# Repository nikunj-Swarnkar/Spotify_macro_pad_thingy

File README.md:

# Spotify Macro-pad Thingy

A custom key macropad with two rotating dials, 6 customisable keys, and an OLED screen. Basically my iteration of the Spotify car thing — but for your desk.

**Project by [nikunj-Swarnkar](https://github.com/nikunj-Swarnkar)** — Firmware by [Nitin-2468-dev](https://github.com/Nitin-2468-dev)

---

## Features

- Two-part case, easy to assemble
- 128×32 OLED display
- 2 × EC11 rotary encoders
- 4 heat-set inserts and bolted case
- 6 mechanical keys

---

## CAD Model

Made in Fusion360. Everything fits together using 4 × M3 bolts and heat-set inserts. The case has two parts: a main body and a front lid.

---

## PCB

Made in KiCad.

**Schematic**

**PCB**

Uses MX-style key switches.

---

## Firmware Overview

The Spotify Marcro-pad Thingy runs **[KMK firmware](https://github.com/KMKfw/kmk_firmware)** on a **[Seeed XIAO RP2040](https://wiki.seeedstudio.com/XIAO-RP2040/)**, paired with a **Python bridge application** that connects Spotify playback data to the keyboard over USB. The device behaves like a mini StreamDeck dedicated to music control.

### Playback Controls

| Key        | Action          |
| ---------- | --------------- |
| Play/Pause | Toggle playback |
| Next       | Next track      |
| Previous   | Previous track  |
| Shuffle    | Toggle shuffle  |
| Repeat     | Toggle repeat   |
| Mute       | Set volume to 0 |

### Encoder Controls

| Encoder   | Function       |
| --------- | -------------- |
| Encoder 1 | Track timeline |
| Encoder 2 | Volume         |

### Key Layout

```
[ Like ]     [ Shuffle ]    [ Minimize ]
[ Rewind ]   [ Play/Pause ] [ Skip ]
```

---

## OLED Display

### Spotify Screen

```
Spotify
Blinding Lights
████░░░░░░ 1:42
```

Displays song title, playback progress bar, and current playback time.

### Volume Screen

```
Volume
██████░░░░ 60%
```

Displayed when adjusting volume.

### Idle Screen

An animated BongoCat appears when nothing is playing.

---

## Album Art Rendering

Album art is fetched from Spotify and processed by the bridge:

1. Download image
2. Resize to 32×32
3. Convert to monochrome
4. Send bitmap to keyboard

The OLED displays the artwork beside the track information.

---

## System Architecture

```
Spotify App
      ↓
Spotify Web API
      ↓
spotify_bridge.exe (Python)
      ↓
USB Serial
      ↓
KMK Firmware
      ↓
Macropad Hardware
      ↓
OLED Display + Controls
```

The bridge application handles Spotify API communication; the firmware handles hardware interaction.

---

## Serial Protocol

Communication between the firmware and bridge uses a lightweight text protocol:

```
SONG|title|artist|position|duration|tempo
VOL|70
IDLE
COVER|bitmap_data
CMD|NEXT
CMD|PLAY
CMD|SEEK|120
```

---

## Firmware

Written using **KMK (Keyboard Module Kit)** on CircuitPython. Main file: `CIRCUITPY/code.py`

**Responsibilities:**

- Scan key matrix
- Handle rotary encoders
- Communicate with bridge over USB
- Render OLED interface
- Control RGB lighting

### Pin Mapping

**Matrix**

| Function | Pin       |
| -------- | --------- |
| COL 0    | D2 / GP28 |
| COL 1    | D3 / GP29 |
| COL 2    | D10 / GP3 |
| ROW 0    | D7 / GP1  |
| ROW 1    | D8 / GP2  |

**Encoder 1 — Volume**

| Signal | Pin       |
| ------ | --------- |
| A      | D0 / GP26 |
| B      | D1 / GP27 |

**Encoder 2 — Track Scrub**

| Signal | Pin      |
| ------ | -------- |
| A      | D6 / GP0 |
| B      | D9 / GP4 |

**OLED**

| Signal | Pin      |
| ------ | -------- |
| SDA    | D4 / GP6 |
| SCL    | D5 / GP7 |

**RGB LEDs:** DATA → D0 / GP26

---

## Folder Structure

| Path | Description |
| ---- | ----------- |
| [`LICENSE`](https://github.com/nikunj-Swarnkar/Spotify_marcro_pad_thingy/blob/main/LICENSE) | MIT License |
| [`README.md`](https://github.com/nikunj-Swarnkar/Spotify_marcro_pad_thingy/blob/main/README.md) | This file |
| [`CIRCUITPY/`](https://github.com/nikunj-Swarnkar/Spotify_marcro_pad_thingy/tree/main/CIRCUITPY) | Firmware files copied to the board |
| [`CIRCUITPY/code.py`](https://github.com/nikunj-Swarnkar/Spotify_marcro_pad_thingy/blob/main/CIRCUITPY/code.py) | Main firmware entry point |
| [`CIRCUITPY/display_manager.py`](https://github.com/nikunj-Swarnkar/Spotify_marcro_pad_thingy/blob/main/CIRCUITPY/display_manager.py) | OLED display logic |
| [`CIRCUITPY/duck_animation.py`](https://github.com/nikunj-Swarnkar/Spotify_marcro_pad_thingy/blob/main/CIRCUITPY/duck_animation.py) | Idle duck animation |
| [`CIRCUITPY/rgb_manager.py`](https://github.com/nikunj-Swarnkar/Spotify_marcro_pad_thingy/blob/main/CIRCUITPY/rgb_manager.py) | RGB LED control |
| [`CIRCUITPY/lib/`](https://github.com/nikunj-Swarnkar/Spotify_marcro_pad_thingy/tree/main/CIRCUITPY/lib) | CircuitPython libraries |
| [`spotify_bridge/`](https://github.com/nikunj-Swarnkar/Spotify_marcro_pad_thingy/tree/main/spotify_bridge) | PC bridge application |
| [`spotify_bridge/spotify_bridge.exe`](https://github.com/nikunj-Swarnkar/Spotify_marcro_pad_thingy/blob/main/spotify_bridge/spotify_bridge.exe) | Compiled bridge (no Python required) |
| [`spotify_bridge/code/spotify_bridge.py`](https://github.com/nikunj-Swarnkar/Spotify_marcro_pad_thingy/blob/main/spotify_bridge/code/spotify_bridge.py) | Bridge source code |
| [`spotify_bridge/code/oled_test_app.py`](https://github.com/nikunj-Swarnkar/Spotify_marcro_pad_thingy/blob/main/spotify_bridge/code/oled_test_app.py) | OLED test utility |
| [`spotify_bridge/code/build_exe.py`](https://github.com/nikunj-Swarnkar/Spotify_marcro_pad_thingy/blob/main/spotify_bridge/code/build_exe.py) | Script to compile the bridge |
| [`spotify_bridge/res/config.json.eg`](https://github.com/nikunj-Swarnkar/Spotify_marcro_pad_thingy/blob/main/spotify_bridge/res/config.json.eg) | Example Spotify API config |
| [`spotify_bridge/res/oled_test_app.exe`](https://github.com/nikunj-Swarnkar/Spotify_marcro_pad_thingy/blob/main/spotify_bridge/res/oled_test_app.exe) | Compiled OLED test utility |
| [`spotify_bridge/res/Duck.gif`](https://github.com/nikunj-Swarnkar/Spotify_marcro_pad_thingy/blob/main/spotify_bridge/res/Duck.gif) | Duck idle animation asset |

---

## Installing Firmware

1. Install CircuitPython for the XIAO RP2040:
   [XIAO RP2040 CircuitPython Guide](https://wiki.seeedstudio.com/XIAO-RP2040-with-CircuitPython/)

2. Copy firmware files to the board at `CIRCUITPY/`.

---

## Spotify Bridge

The bridge software connects the keyboard to Spotify.

**Location:** `spotify_bridge/`

**Run:**

```
spotify_bridge.exe
```

Or:

```
python spotify_bridge.py
```

### Spotify API Setup

1. Create an application at the [Spotify Developer Dashboard](https://developer.spotify.com/dashboard)
2. Add the redirect URI: `http://localhost:8888/callback`
3. Copy your credentials into `spotify_bridge/res/config.json`

---

## Running the System

1. Plug the macropad into USB
2. Launch `spotify_bridge.exe`
3. Start Spotify
4. Use the macropad to control playback

---

## Future Improvements

- Audio visualizer on OLED
- RGB BPM lighting improvements
- System tray bridge application
- Multi-service support (YouTube Music, Apple Music)
- Enhanced OLED UI

---

## Bill of Materials

| Qty | Item                      |
| --- | ------------------------- |
| 6×  | Cherry MX switches        |
| 6×  | DSA keycaps               |
| 4×  | M3×5×4 heat-set inserts   |
| 4×  | M3×16mm SHCS bolts        |
| 6×  | 1N4148 DO-35 diodes       |
| 1×  | 0.91" 128×32 OLED display |
| 2×  | EC11 rotary encoders      |
| 1×  | Seeed XIAO RP2040         |
| 1×  | Case (2 printed parts)    |

---

## License

[MIT License](https://github.com/nikunj-Swarnkar/Spotify_marcro_pad_thingy/blob/main/LICENSE)

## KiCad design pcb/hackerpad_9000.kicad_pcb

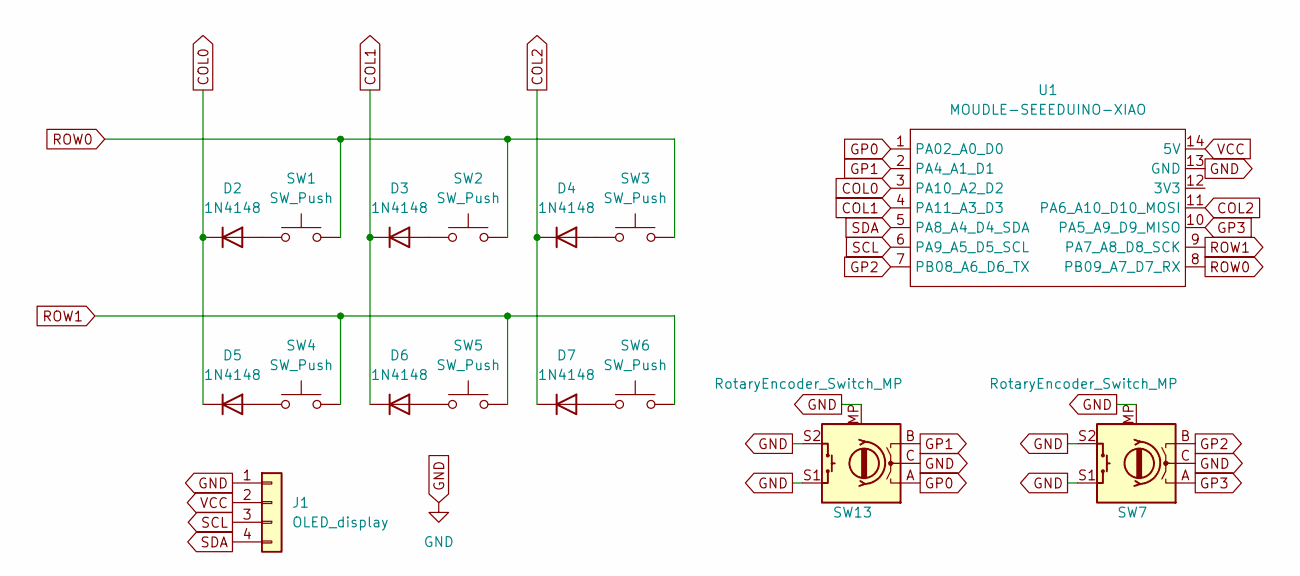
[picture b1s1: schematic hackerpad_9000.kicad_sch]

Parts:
D2, D3, D4, D5, D6, D7: 1N4148; D_DO-35_SOD27_P7.62mm_Horizontal
J1: OLED_display; SSD1306-0.91-OLED-4pin-128x32
SW1, SW2, SW3, SW4, SW5, SW6: SW_Push; SW_Cherry_MX_1.00u_PCB
SW7, SW13: RotaryEncoder_Switch_MP; RotaryEncoder_Alps_EC11E-Switch_Vertical_H20mm
U1: MOUDLE-SEEEDUINO-XIAO; XIAO-Generic-Hybrid-14P-2.54-21X17.8MM

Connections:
COL0: D2.1 (K), D5.1 (K), U1.3 (PA10_A2_D2)
COL1: D3.1 (K), D6.1 (K), U1.4 (PA11_A3_D3)
COL2: D4.1 (K), D7.1 (K), U1.11 (PA6_A10_D10_MOSI)
GND: J1.1 (GND), SW7.C, SW7.MP, SW7.S1, SW7.S2, SW13.C, SW13.MP, SW13.S1, SW13.S2, U1.13 (GND)
GP0: SW13.A, U1.1 (PA02_A0_D0)
GP1: SW13.B, U1.2 (PA4_A1_D1)
GP2: SW7.B, U1.7 (PB08_A6_D6_TX)
GP3: SW7.A, U1.10 (PA5_A9_D9_MISO)
unnamed: D2.2 (A), SW1.1
unnamed: D3.2 (A), SW2.1
unnamed: D4.2 (A), SW3.1
unnamed: D5.2 (A), SW4.1
unnamed: D6.2 (A), SW5.1
unnamed: D7.2 (A), SW6.1
ROW0: SW1.2, SW2.2, SW3.2, U1.8 (PB09_A7_D7_RX)
ROW1: SW4.2, SW5.2, SW6.2, U1.9 (PA7_A8_D8_SCK)
SCL: J1.3 (SCL), U1.6 (PA9_A5_D5_SCL)
SDA: J1.4 (SDA), U1.5 (PA8_A4_D4_SDA)
VCC: J1.2 (VCC), U1.14 (5V)

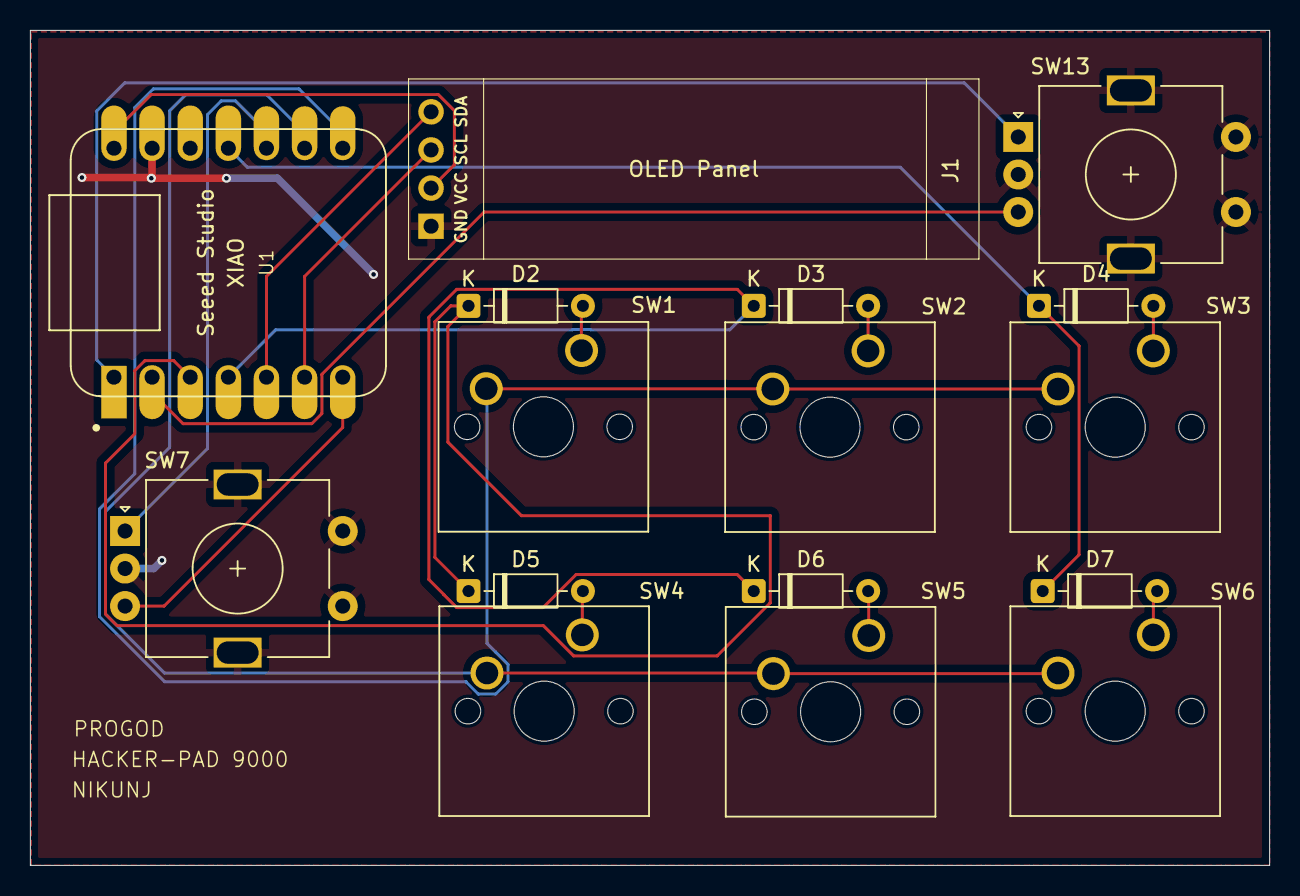
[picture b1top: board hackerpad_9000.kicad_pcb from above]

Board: 2 copper layers, 82.6 x 55.6 mm, 16 parts (0 on the bottom side), 19 nets.

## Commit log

2026-03-11 Revise README for Hackerpad 9000
    Updated README to improve formatting and clarity.
2026-03-11 Revise BOM list and clean up README content
    Updated BOM section and removed unnecessary text.
2026-03-11 Update PCB image filename in README
    Fix image filename for PCB in README.
2026-03-11 Change CAD model image reference
    Updated image reference in README to hackerpadd.
2026-03-12 Fix typos and improve README clarity
    Corrected spelling and grammar in the README.
2026-03-13 Expand README with firmware and project details
    Added detailed firmware overview, features, system architecture, hardware components, key layout, OLED display information, serial protocol, and installation instructions for the Spotify macropad pro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
2026-03-13 Refactor README for improved clarity and structure
    Updated the README to enhance the structure and clarity of the firmware overview, features, and installation instructions.
2026-03-13 Update project name in README
2026-03-13 firmware
2026-03-13 Improve README with author link and image URLs
    Updated author attribution and replaced local image links with URLs for better accessibility.
2026-03-13 Enhance README with firmware installation instructions
    Added detailed installation and setup instructions for the firmware and Spotify bridge software, including steps for installing CircuitPython, copying firmware files, installing required libraries, a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
2026-03-13 Add README for custom Spotify macropad project
    Added detailed documentation for the custom macropad project, including features, CAD model, PCB design, firmware overview, and installation instructions.
2026-03-13 Update README.md for project details and links
2026-03-13 Rename pcb.f3z to cad.f3z
2026-03-15 updating to new PCB
2026-03-15 updating to new Gerbers.zip file
